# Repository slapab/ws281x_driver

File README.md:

## Short description

> NOTE:
>
>The project's name suggests that it should work on all WS281x types LEDs. That was primary intention, but presented driver has been tested only with WS2812B LEDs.

This repository contains driver for WS2812B LED controller where SPI peripheral is using to handle transmission timing. It is written in C++11 and it is using [*bit banding*](http://infocenter.arm.com/help/index.jsp?topic=/com.arm.doc.ddi0337h/Behcjiic.html) and DMA to achieve two things:

 - relative small memory usage for storing, manipulating and transfering colors for each LED in the chain
 - using hardware during transmission as often as possible (unfortunately not in 100%)

As a result, the current version to store RGB colors and to transmit them to LEDs requires memory of size:

 - 2 x LEDs count x 3 bytes
 Two buffers to store each LED color in the chain of size *LEDs Count*:
    - multiplying by 2 because during ongoing transmission the driver operates on the second buffer
    - multiplying by 3 to store LEDs colors
 - 2 x 12 bytes

 These buffers are being used during transmission and each contain prepared RGB color for one LED at the time. DMA copies these bytes to SPI and *end of transfer interrupt* is used to convert color for next LED in chain. So, this is not fully hardware transmission, but interrupt handling that prepares next LED data to transmit takes about 6µs while CPU is running with 48 MHz clock.
 - 2 x (12 x 2 x *size of pointer*) bytes

  These tables store *bit banding* regions that correspond to specific bits for each transmitting buffer's byte.

## Detailed description

### Driver implementation
* #### SPI
Using SPI peripheral to drive WS281x LEDs is a well known solution. The idea is simple, each transmitted byte through SPI interface contains two bits of color, so to transmit one RGB color for one LED, there is need to send 12 'encoded' bytes.
Because 4 bits during SPI transmission represents one bit in WS281x interface, care must be taken while configuring clock for SPI peripheral:
    - transmission frequency of one bit of WS281x interface must be as close as to 800 kHz - but taking into consideration tolerances, acceptable transmission frequencies are in the range from 646 kHz to 1.05 MHz.
    - for example, using 48 MHz to clock SPI peripheral and using prescaler of value 16, each bit will be transmitted with 3MHz frequency. Because 4 bits sent by SPI are just one bit of WS281x's color, so the average frequency for transmitting one bit of LED color is 750kHz.

* #### Bit-banding
[Bit banding is well explained here.](http://infocenter.arm.com/help/index.jsp?topic=/com.arm.doc.ddi0337h/Behcjiic.html)

  Two buffers - each 12 bytes long - are being used to transmit colors to LEDs. In the table below I have marked positions of two bits of color inside one transmitting byte. Transmitting bits 7:4 represents one bit of transmitting color and transmitting bits 3:0 represents next bit of color. If bit marked as 'X' is set to '0' then WS281x controller reads bits 7:4 or 3:0 as color's bit '0', otherwise reads them as '1'.

  <table>
    <tr>
        <td>bit</td>
        <td>7</td><td>6</td><td>5</td><td>4</td><td>3</td><td>2</td><td>1</td><td>0</td>
    </tr>
    <tr>
    	<td>value</td>
        <td>1</td><td><b style="color:green;">X</b></td><td>0</td><td>0</td><td>1</td><td><b style="color:green;">X</b></td><td>0</td><td>0</td>
    </tr>
  </table>

  Presented implementation prepares the table with pointers to bit band regions for 2nd and 6th bit for each byte inside transmitting buffers. Thanks to that writing under appropriate pointer any value greater than 0 sets corresponding bit to '1', and writing zero sets corresponding bit to '0'. Because writing operation to bit banding region is just like STR instruction, so it is quite fast.

* #### DMA

  Current implementation is using two DMA channels:
    1. Prior to send any color, need to convert RGB data into transmitting buffers. Like mentioned at the beginning, one LED color (RGB) is converted and stored inside of 12 bytes inside the transmitting buffer. Just before transmission is being started, the application converts colors of two LEDs and places them into transmitting buffers. Then transmission is started and 12 bytes of first buffer are being sent to the SPI peripheral by the DMA. During *each end of transfer interrupt* the next transmission (from the second buffer) is being started only if _end of transmission flag_ is not set. Next, still inside interrupt routine, checks if there is any color to send - if is, then RGB value is converted and stored inside of just freed transmitting buffer.
    2. There are two buffers which store colors for LEDs. Driver always uses one of them at the time. When *send()* was called then the driver does:
        - buffer which was just modified will be used as colors source during transmission - it is just 'renamed' to *transmitting* buffer and the second buffer (which was in the background) will be 'renamed' to *active* buffer, and there changes made by called API methods will be applied since now.
        - synchronizing these two buffers to have the same content - this ensures that next call to API that modifies LEDs colors will operate on the same content as was before calling *send()* method. That operation is done by the second channel of the DMA. As the result, the application can modify LED's colors while transmission of the previous 'snapshot' is in progress.

### PC visualization application

When I've implemented driver to version when it worked quite stable with a few animations running on 300 LEDs strip, I have put hardware to work continuously as a decoration. I have had to figure out how to test new code with lack of fully working hardware. The idea was to separate driver layer from transmission layer, so the PC application has to just simulate transmission process and LEDs. PC visualization application has been made with Qt5 and C++14 as an QtCreator4 project.

When main thread (GUI) is being started it constructs QWidget with small squares which are being painted horizontally. Each square represents one LED. Next, the new thread is created which uses WS281x driver API to run animations (that thread is equivalent to microcontroller program). The PC's transmission layer is just a simple method that runs in the another thread. Its job is send colors bytes provided by the WS281x driver to the main (GUI) thread and simulates transmission time.

PC visualization application sources are stored in [pc\_visualization\_proj](./pc_visualization_proj) subdirectory.

### Voltage converter - simple KiCAD project.

To ensure proper data signal shape (conversion level 3.3V -> 5V) I've designed simple hardware using parts that I already had on the 'shelf'. It uses two CMOS NOT gates connected in series and powered from 5V. Input signal from MCU is connected to the first gate through capacitor placed in series. Project files are stored in [KiCAD\_ws281x\_level\_converter](./KiCAD_ws281x_level_converter) subdirectory.

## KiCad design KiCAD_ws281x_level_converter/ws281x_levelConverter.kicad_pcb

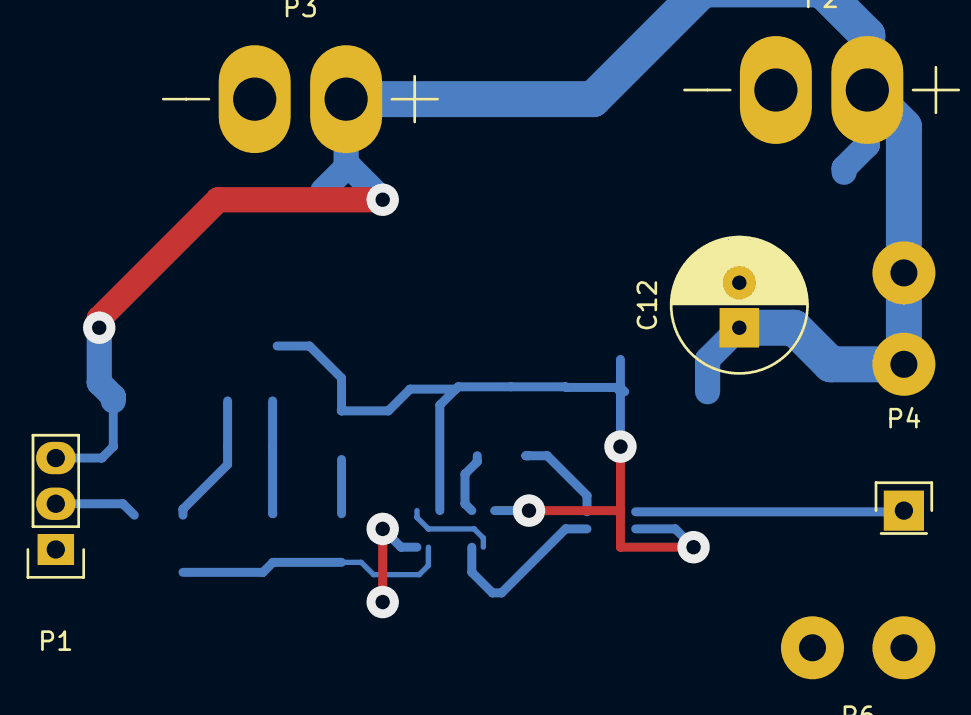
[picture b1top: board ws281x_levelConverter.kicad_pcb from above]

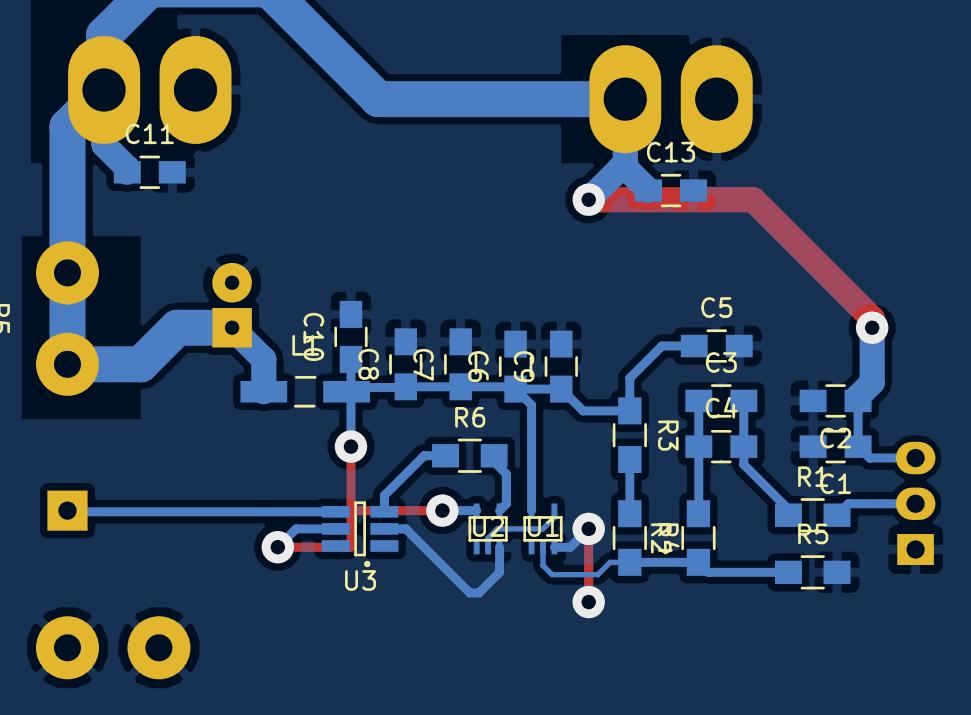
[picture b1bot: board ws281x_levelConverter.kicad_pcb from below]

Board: 2 copper layers, 29 parts (23 on the bottom side), 12 nets.

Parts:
C1: 4.7u; C_0805_HandSoldering
C2, C3, C5, C6, C7, C10, C11, C13: 100n; C_0805_HandSoldering
C4: 100n (opt); C_0805_HandSoldering
C8: 1u; C_0805_HandSoldering
C9: 1u (opt); C_0805_HandSoldering
C12: 470u; C_Radial_D7.5_L11.2_P2.5
L1: bead; Choke_SMD_1206_Handsoldering
P1: stm32f103; Pin_Header_Straight_1x03
P2, P3: SUPPLY_IN; SupplySocket
P4: WS281xDIN; Pin_Header_Straight_1x01
P5: WS281x_5V; SolderWirePad_2x_1-5mmDrill
P6: WS281x_GND; SolderWirePad_2x_1-5mmDrill
R1: 47; R_0805_HandSoldering
R2: 100; R_0805_HandSoldering
R3, R4, R5: 10k; R_0805_HandSoldering
R6: 470; R_0805_HandSoldering
U1, U2: 74AHC1G04; SOT-353
U3: USBLC6-2; SOT-23-6_Handsoldering

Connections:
+5V: C1.1, C2.1, C11.1, C12.1, C13.1, L1.1, P1.3, P2.1, P3.1, P5.1
DATA: P1.2, R1.2
FilteredSupply: C5.1, C6.1, C7.1, C8.1, C9.1, C10.1, L1.2, R3.1, U1.5, U2.5, U3.5
GND: C1.2, C2.2, C5.2, C6.2, C7.2, C8.2, C9.2, C10.2, C11.2, C12.2, C13.2, P1.1, P2.2, P3.2, P6.1, R5.2, U1.3, U2.3, U3.2
unnamed: C3.1, C4.1, R2.2
unnamed: C3.2, C4.2, R1.1
unnamed: P4.1, U3.4
unnamed: R2.1, R4.2, R5.1, U1.2
unnamed: R3.2, R4.1
unnamed: R6.1, U3.3
unnamed: R6.2, U2.4
unnamed: U1.4, U2.2

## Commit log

2016-12-22 Updated .gitignore
2016-12-24 New debug configuration
2016-12-24 Added animation strategy class and an interface for each specific animation class that can be run by strategy.
2016-12-24 Added pseudo random number generator with ability to seed with data from ADC that scans floating analog input, but currently, that doesn't work because the conversion can't be started or can't be com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
2016-12-26 Fixed problem with setting the last LED
2016-12-26 Updated pseudorndomdotsanimation
2016-12-26 Fixed wrong setting of modified_end pointer when calling fill() method
2016-12-27 Added movingpixelsanimation. Updated others and main.c
2016-12-27 Added fallingsnowanimation
2016-12-27 Enabled size optimaliation
2016-12-27 Added operator-() to ColorRGB class
2016-12-27 Added inc() method that incremetnts color with respect to maximum values
2016-12-27 Added walkingotsanimation. Also changed c++ compiler settings to use next iso stanard.
2016-12-28 Added moveForward() and moveBackward()
2016-12-28 Added next animation
2016-12-28 Added some time when brightness is is at 0% and replaced green.
2016-12-29 Fixed moveForward and moveBackward - setting modified start and modified end pointers
2017-01-01 Added qt5-based project that makes visualtization of animations on PC without any hardware.
2017-01-01 Added KiCAD based project that describes the level shifter for WS281x LEDs (based on two CMOS inverters).
2017-03-05 Binaries for stm32f1x
2017-03-10 Added project description.
